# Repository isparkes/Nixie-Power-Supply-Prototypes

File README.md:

# Nixie HV Supply

KiCad projects for a small 5 V → ~170 V switching supply, sized to drop onto a nixie
clock board. Two layouts of the same circuit are kept here side by side.

> **Provenance:** I make no claims to these designs. I found them online and redrew them
> in KiCad so I could build them. No license, no copyright — do whatever you like with
> the files in this repo. Recently there have been problems finding a supplier for the 
> transformer used, the original sourse was Tokyo Coil if I remember correctly, but in 
> recent times, the price of these parts has become unpredeictable. Perhaps there is a 
> better shource now.

Due to the suuply chain problems, I eventually settled on this design for my clocks:

https://github.com/isparkes/HVPS_SMD

which uses a custom wound transformer and provides good results for a low price.

## Contents

| Folder | Project | Notes |
| --- | --- | --- |
| `Alternative1/` | `NixiePS1` | "Nixie HV power supply alternative 1" |
| `Alternative2/` | `NixiePS2` | "Nixie HV power supply alternative 2" |

Both carry the same schematic and the same bill of materials; they differ only in how
the board is routed. Pick whichever lays out better for your build.

## The board

- 25 × 20 mm, 2 copper layers, 1.6 mm FR4
- Boost/flyback converter around a MAX668 PWM controller
- `TPH1R403NL` N-channel switch, `TTRN-060S` transformer, `ES1JL` rectifier
- Output filtered by a 2.2 µF / 250 V electrolytic
- Silkscreen marks it `HVSMPS 1.0Adj`

### Connectors

| Connector | Pins | Function |
| --- | --- | --- |
| `J1` (IN) | `5V`, `GND` | Supply in |
| `J2` (OUT) | `GND`, `RT`, `170V` | HV out, plus the adjust pin |

`J2` pin 2 is `Rext`: fit a resistor from it to ground to raise the output voltage.
Left open, the board delivers roughly 170 V.

## Bill of materials

| Ref | Value | Footprint |
| --- | --- | --- |
| U3 | MAX668 | MAX668 |
| Q1 | TPH1R403NL | TPH1R403NL |
| T1 | TTRN-060S | TTRN-060S |
| D4 | ES1JL | SOD-123F |
| C1 | 220 pF | 0805 |
| C15 | 220 µF 16 V | CP_Elec_SMD_6.3×7.7 |
| C17 | 1 µF | 0805 |
| C18 | 220 nF | 0805 |
| C19 | 2.2 µF 250 V | CP_Elec_6.3×5.3 |
| R8 | 0R001 | 1206 |
| R9 | 499 k | 0805 |
| R10 | 69.8 k | 0805 |
| R11 | 10 M | 0805 |
| J1 | IN | Header MA02 (edge) |
| J2 | OUT | Header MA03 (edge) |
| FID1, FID2 | Fiducial | 0.75 mm / 1.5 mm mask |

R8 is the current-sense shunt, R9 sets the switching frequency, and R10/R11 form the
output feedback divider — `Rext` on `J2` sits across the lower leg to trim the voltage
upwards.

## Opening the files

Made with **KiCad 10**. Earlier versions will not read these files.

Symbols come from a `NixieClockMasterNew` library and footprints from `NixieClockMaster`,
which live outside this repo — `fp-lib-table` and `sym-lib-table` point at them. Without
those libraries the schematic and board still open and the cached footprints still
render, but library links will show as missing.

Autosave backups, CAM output, and generated zips are gitignored.

## Safety

The output side runs at a few hundred volts and the bulk capacitor holds charge after
power is removed. Discharge it before handling the board.

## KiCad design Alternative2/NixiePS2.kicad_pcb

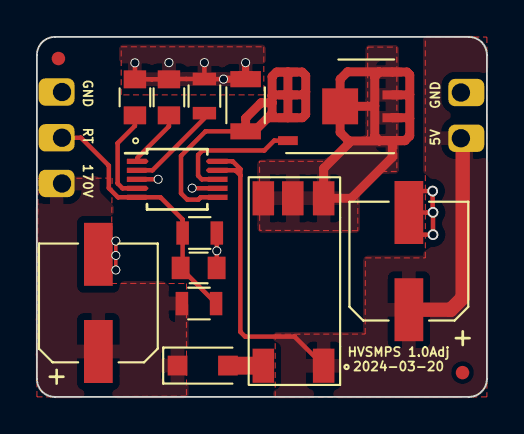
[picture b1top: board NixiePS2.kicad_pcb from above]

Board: 2 copper layers, 25.0 x 20.0 mm, 17 parts (0 on the bottom side), 11 nets.

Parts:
C1: 220pF; C_0805
C15: 220uF 16V; CP_Elec_SMD_6.3x7.7
C17: 1uF; C_0805
C18: 220nF; C_0805
C19: 2.2uF 250V; CP_Elec_6.3x5.3
D4: ES1JL; D_SOD-123F
FID1, FID2: Fiducial; Fiducial_0.75mm_Mask1.5mm
J1: IN; Header_MA02-Edge
J2: OUT; Header_MA03-Edge
Q1: TPH1R403NL
R8: 0R001; R_1206
R9: 499k; R_0805
R10: 69.8k; R_0805
R11: 10M; R_0805
T1: TTRN-060S
U3: MAX668

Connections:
/EXT: Q1.4 (G), U3.8 (EXT)
/FB: C1.1, J2.2, R10.1, R11.1, U3.5 (FB)
/FET_DRAIN: Q1.5 (D), Q1.6 (D), Q1.7 (D), Q1.8 (D), Q1.9 (D), T1.3 (SA), T1.4 (NC), T1.5 (AA)
/FET_SOURCE: Q1.1 (S), Q1.2 (S), Q1.3 (S), R8.2, U3.6 (CS)
/FREQ: R9.1, U3.2 (FREQ)
/HV: C19.1, D4.1 (K), J2.1, R11.2
/LDO: C17.1, U3.1 (LDO)
/REF: C18.1, U3.4 (REF)
/VIN: C15.1, J1.2, T1.1 (AB), U3.9 (VCC), U3.10 (SHDN)
GND: C1.2, C15.2, C17.2, C18.2, C19.2, J1.1, J2.3, R8.1, R9.2, R10.2, U3.3 (GND), U3.7 (PGEND)
unnamed: D4.2 (A), T1.2 (SB)
